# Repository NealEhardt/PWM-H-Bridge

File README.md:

# PWM H-Bridge

This repository includes the KiCad project and Gerber files for a PCB that converts DC➡AC to transmitt wireless power through a coil. It generates a PWM signal in the KHz range to control an H-bridge. Frequency is adjustible with a knob.

This repo contains **rev. 2** which is _nearly identical_ to the above image, except I fixed an issue where the diodes were reversed.

I got the schematic from [DIY Wireless Energy Transfer System by Great Scott](https://www.instructables.com/id/DIY-Wireless-Energy-Transfer-System/). See that page for bill of materials and a highly informative video tutorial.

I copied Scott's schematic into KiCad 5.1.2 and laid out the PCB. I did **not** use the same identifier numbers as he did, but the part counts are identical. Part names are silkscreened on the PCB so it should be easy to assemble.

## Choosing capacitors for coils

The transmit and receive coils each need a capacitor nearby to make them resonate. The transmitter capacitor goes in series and the receiver capacitor goes in parallel.

Look in the coils' datasheets for the plot of Q-factor vs frequency, and choose a frequency that maximizes the Q of both coils. Also look up the coils' inductance (L).

For each coil, calculate `C = 1 / (4π²f²L)`. For example, `C = 1 / (4π²(150 KHz)²(24 µH))` = [47 nF](https://www.google.com/search?q=1%2F%284*pi%5E2*%28150+KHz%29%5E2*%2824+%C2%B5H%29%29+in+nanofarads).

Non-polarized capacitors must be used because the current is alternating.

## Ordering the PCB

You can upload [the Gerber zip](Plot/PWM-H-Bridge.zip) file to most PCB manufacturers. I had success ordering from Seeed Studio.

## Testing the transmitter

You need a 12V DC power supply (relatively weak) and a DC VCC supply (relatively strong). You can just use the same 12V supply for both.

If you're going to test with no receiver or a misaligned receiver, be sure to use a current-limited power supply for VCC. Otherwise, the transmitter will draw lots of current and you're likely to burn something up.

## Disclaimer

Electricity is dangerous and you might hurt yourself, but that's not my problem. Be careful, have fun, and please post any issues you have. You may freely modify and copy this work, in part or in whole, with or without attribution.

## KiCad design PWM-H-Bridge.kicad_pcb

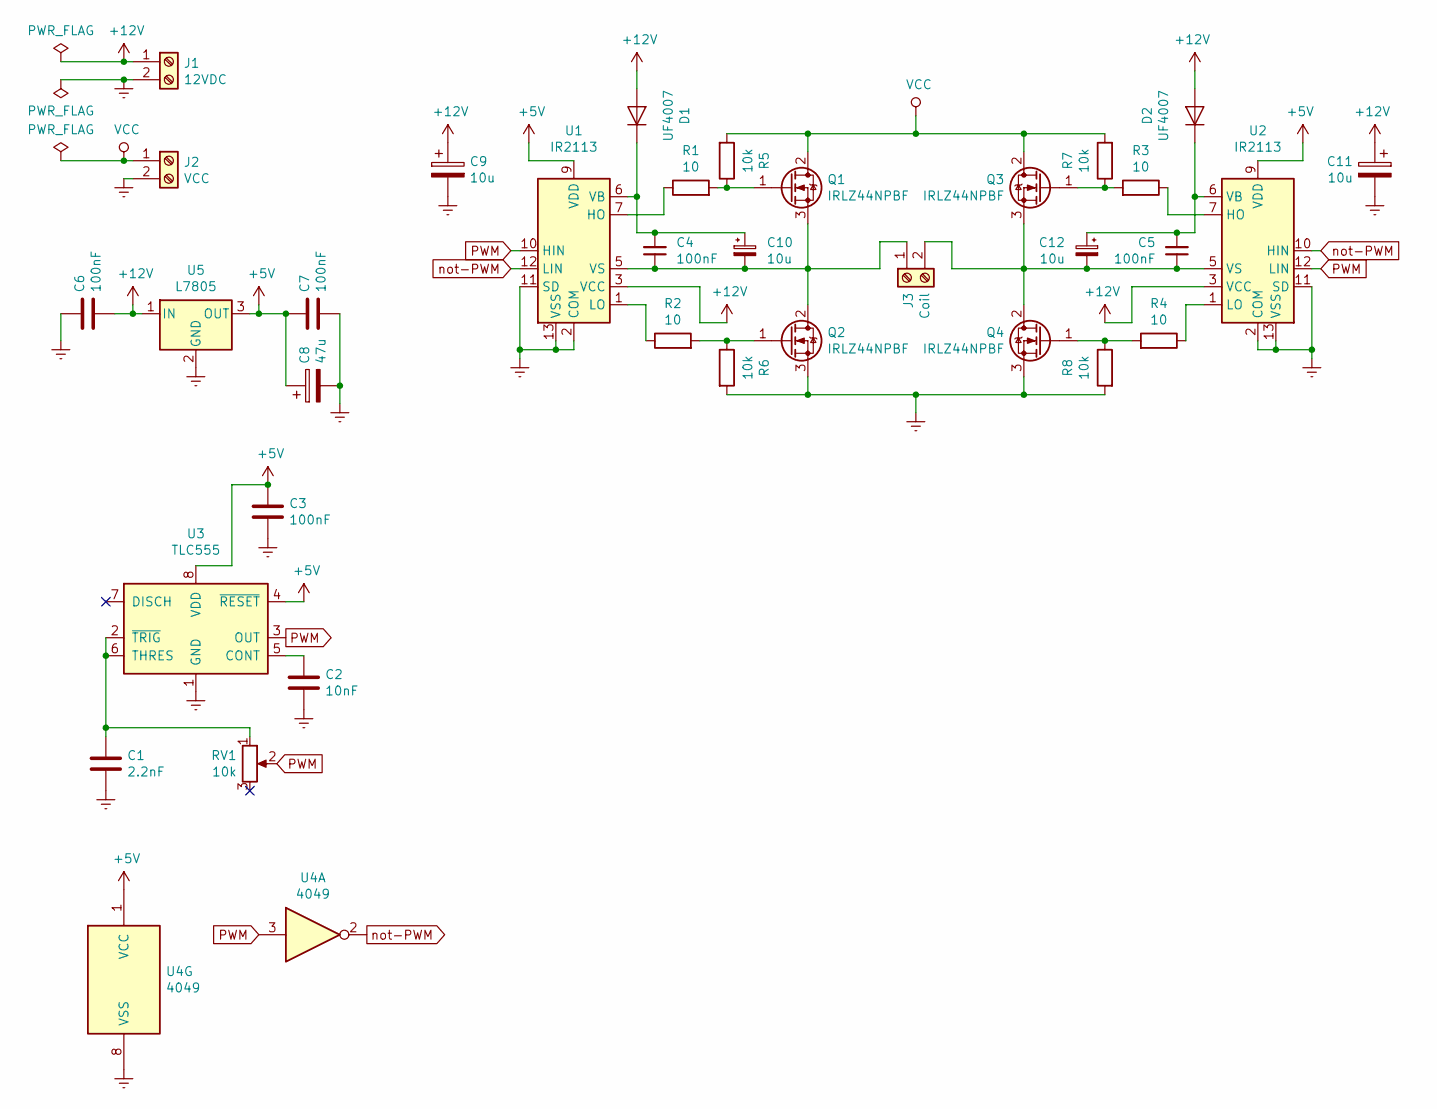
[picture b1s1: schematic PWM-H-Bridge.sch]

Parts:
C1: 2.2nF; C_Rect_L7.0mm_W2.5mm_P5.00mm
C2: 10nF; C_Rect_L4.0mm_W2.5mm_P2.50mm
C3, C4, C5, C6, C7: 100nF; C_Rect_L4.0mm_W2.5mm_P2.50mm
C8: 47u; CP_Radial_D5.0mm_P2.00mm
C9, C10, C11, C12: 10u; CP_Radial_D5.0mm_P2.00mm
D1, D2: UF4007; D_DO-41_SOD81_P7.62mm_Horizontal
J1: 12VDC; TerminalBlock_Phoenix_PT-1,5-2-5.0-H_1x02_P5.00mm_Horizontal
J2: VCC; TerminalBlock_Phoenix_PT-1,5-2-5.0-H_1x02_P5.00mm_Horizontal
J3: Coil; TerminalBlock_Phoenix_PT-1,5-2-5.0-H_1x02_P5.00mm_Horizontal
Q1, Q2, Q3, Q4: IRLZ44NPBF; TO-220-3_Vertical
R1, R2, R3, R4: 10; R_Axial_DIN0207_L6.3mm_D2.5mm_P10.16mm_Horizontal
R5, R6, R7, R8: 10k; R_Axial_DIN0207_L6.3mm_D2.5mm_P10.16mm_Horizontal
RV1: 10k; Potentiometer_Bourns_3296W_Vertical
U1, U2: IR2113; DIP-14_W7.62mm
U3: TLC555; DIP-8_W7.62mm
U4: 4049; DIP-16_W7.62mm
U5: L7805; TO-220-3_Vertical

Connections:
+5V: C3.1, C7.2, C8.1, U1.9 (VDD), U2.9 (VDD), U3.4 (~RESET), U3.8 (VDD), U4.1 (VCC), U5.3 (OUT)
+12V: C6.1, C9.1, C11.1, D1.2 (A), D2.2 (A), J1.1, U1.3 (VCC), U2.3 (VCC), U5.1 (IN)
Earth: C1.2, C2.2, C3.2, C6.2, C7.1, C8.2, C9.2, C11.2, J1.2, J2.2, Q2.3 (S), Q4.3 (S), R6.2, R8.2, U1.2 (COM), U1.11 (SD), U1.13 (VSS), U2.2 (COM), U2.11 (SD), U2.13 (VSS), U3.1 (GND), U4.8 (VSS), U5.2 (GND)
unnamed: C1.1, RV1.1, U3.2 (~TRIG), U3.6 (THRES)
unnamed: C2.1, U3.5 (CONT)
unnamed: C4.2, C10.1, D1.1 (K), U1.6 (VB)
unnamed: C4.1, C10.2, J3.1, Q1.3 (S), Q2.2 (D), U1.5 (VS)
unnamed: C5.2, C12.1, D2.1 (K), U2.6 (VB)
unnamed: C5.1, C12.2, J3.2, Q3.3 (S), Q4.2 (D), U2.5 (VS)
unnamed: Q1.1 (G), R1.2, R5.1
unnamed: Q2.1 (G), R2.2, R6.1
unnamed: Q3.1 (G), R3.2, R7.1
unnamed: Q4.1 (G), R4.2, R8.1
unnamed: R1.1, U1.7 (HO)
unnamed: R2.1, U1.1 (LO)
unnamed: R3.1, U2.7 (HO)
unnamed: R4.1, U2.1 (LO)
PWM: RV1.2, U1.10 (HIN), U2.12 (LIN), U3.3 (OUT), U4.3
VCC: J2.1, Q1.2 (D), Q3.2 (D), R5.2, R7.2
not-PWM: U1.12 (LIN), U2.10 (HIN), U4.2

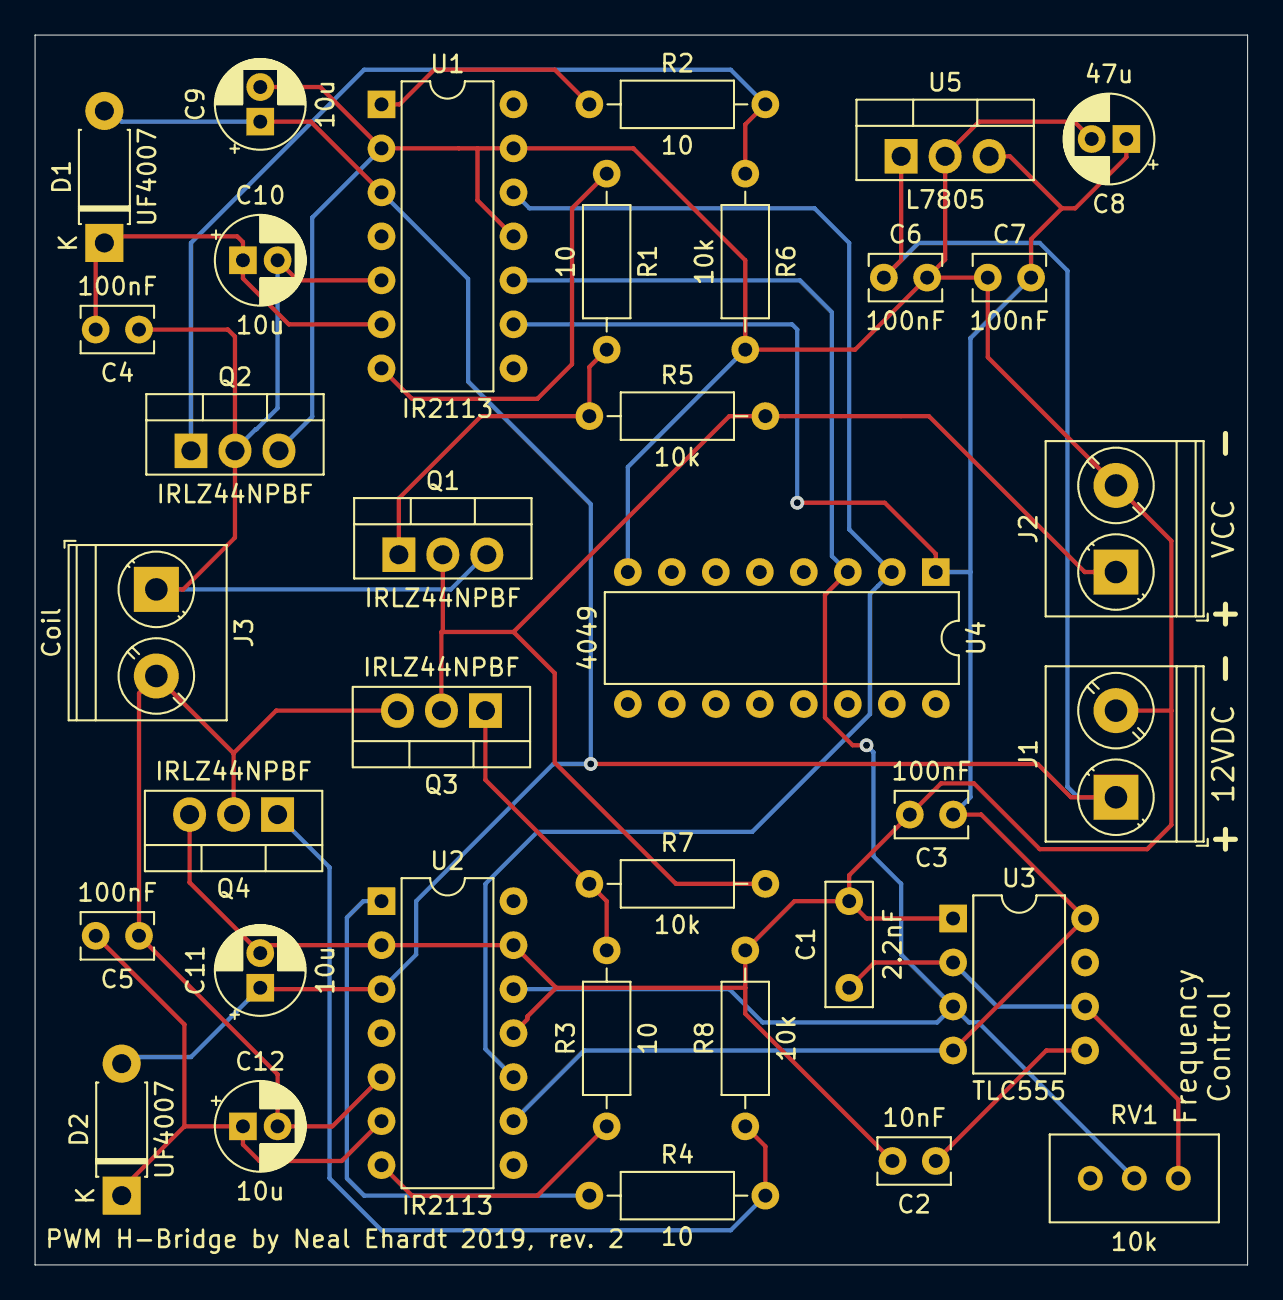
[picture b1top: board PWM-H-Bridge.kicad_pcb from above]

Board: 2 copper layers, 70.0 x 71.0 mm, 35 parts (0 on the bottom side), 20 nets.

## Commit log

2019-09-21 Rev. 2
